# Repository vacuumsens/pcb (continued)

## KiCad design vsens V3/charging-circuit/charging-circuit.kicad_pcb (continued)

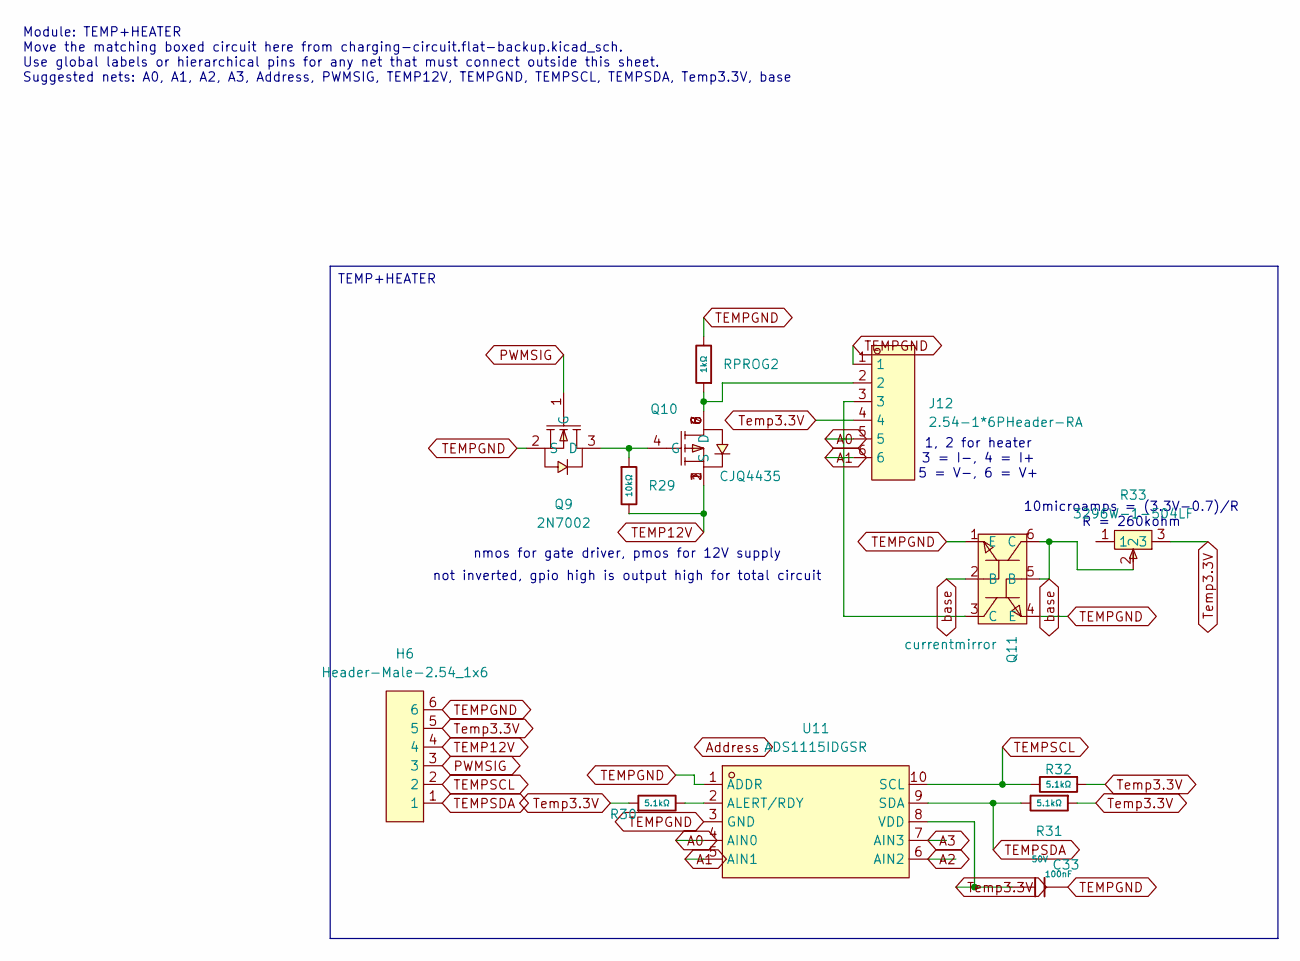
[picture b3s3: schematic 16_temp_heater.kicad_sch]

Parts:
C33: 100nF; C_0603; Voltage Rated 50V; Tolerance ±10%; Part CC0603KRX7R9BB104; LCSC C14663
H6: Header-Male-2.54_1x6; HDR-TH_6P-P2.54-V-M-1; LCSC Part C37208
J12: 2.54-1*6PHeader-RA; HDR-TH_6P-P2.54-H-M-W10.0; LCSC Part C56816
Q9: 2N7002; SOT-23-3_L2.9-W1.3-P1.90-LS2.4-BR; LCSC Part C8545
Q10: CJQ4435; SOP-8_L5.0-W4.0-P1.27-LS6.2-BL; LCSC Part C114076
Q11: currentmirror; SOT-363-6_L2.2-W1.3-P0.65-LS2.1-BL; LCSC Part C41375126
R29: 10kΩ; R_0603; Overload Voltage (Max) 75V; Tolerance ±1%; Part 0603WAF1002T5E; LCSC C25804
R30, R31, R32: 5.1kΩ; R_0603; Overload Voltage (Max) 75V; Tolerance ±1%; Part 0603WAF5101T5E; LCSC C23186
R33: 3296W-1-504LF; RES-ADJ-TH_3296W; LCSC Part C83694
RPROG2: 1kΩ; R_0603; Overload Voltage (Max) 75V; Tolerance ±1%; Part 0603WAF1001T5E; LCSC C21190
U11: ADS1115IDGSR; MSOP-10_L3.0-W3.0-P0.50-LS5.0-BL; LCSC Part C37593

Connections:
A0: J12.5, U11.4 (AIN0)
A1: J12.6, U11.5 (AIN1)
A2: U11.6 (AIN2)
A3: U11.7 (AIN3)
unnamed: J12.2, Q10.5 (D), Q10.6 (D), Q10.7 (D), Q10.8 (D), RPROG2.1
unnamed: J12.3, Q11.3 (C)
unnamed: Q9.3 (D), Q10.4 (G), R29.1
unnamed: R30.2, U11.2 (ALERT/RDY)
PWMSIG: H6.3, Q9.1 (G)
TEMP12V: H6.4, Q10.1 (S), Q10.2 (S), Q10.3 (S), R29.2
TEMPGND: C33.2, H6.6, J12.1, Q9.2 (S), Q11.1 (E), Q11.4 (E), RPROG2.2, U11.1 (ADDR), U11.3 (GND)
TEMPSCL: H6.2, R32.2, U11.10 (SCL)
TEMPSDA: H6.1, R31.2, U11.9 (SDA)
Temp3.3V: C33.1, H6.5, J12.4, R30.1, R31.1, R32.1, R33.3, U11.8 (VDD)
base: Q11.2 (B), Q11.5 (B), Q11.6 (C), R33.2

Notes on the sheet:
1, 2 for heater 3 = I-, 4 = I+ 5 = V-, 6 = V+
10microamps = (3.3V-0.7)/R R = 260kohm
not inverted, gpio high is output high for total circuit
Module: TEMP+HEATER Move the matching boxed circuit here from charging-circuit.flat-backup.kicad_sch. Use global labels or hierarchical pins for any net that must connect outside this sheet. Suggested nets: A0, A1, A2, A3, Address, PWMSIG, TEMP12V, TEMPGND, TEMPSCL, TEMPSDA, Temp3.3V, base
nmos for gate driver, pmos for 12V supply
TEMP+HEATER

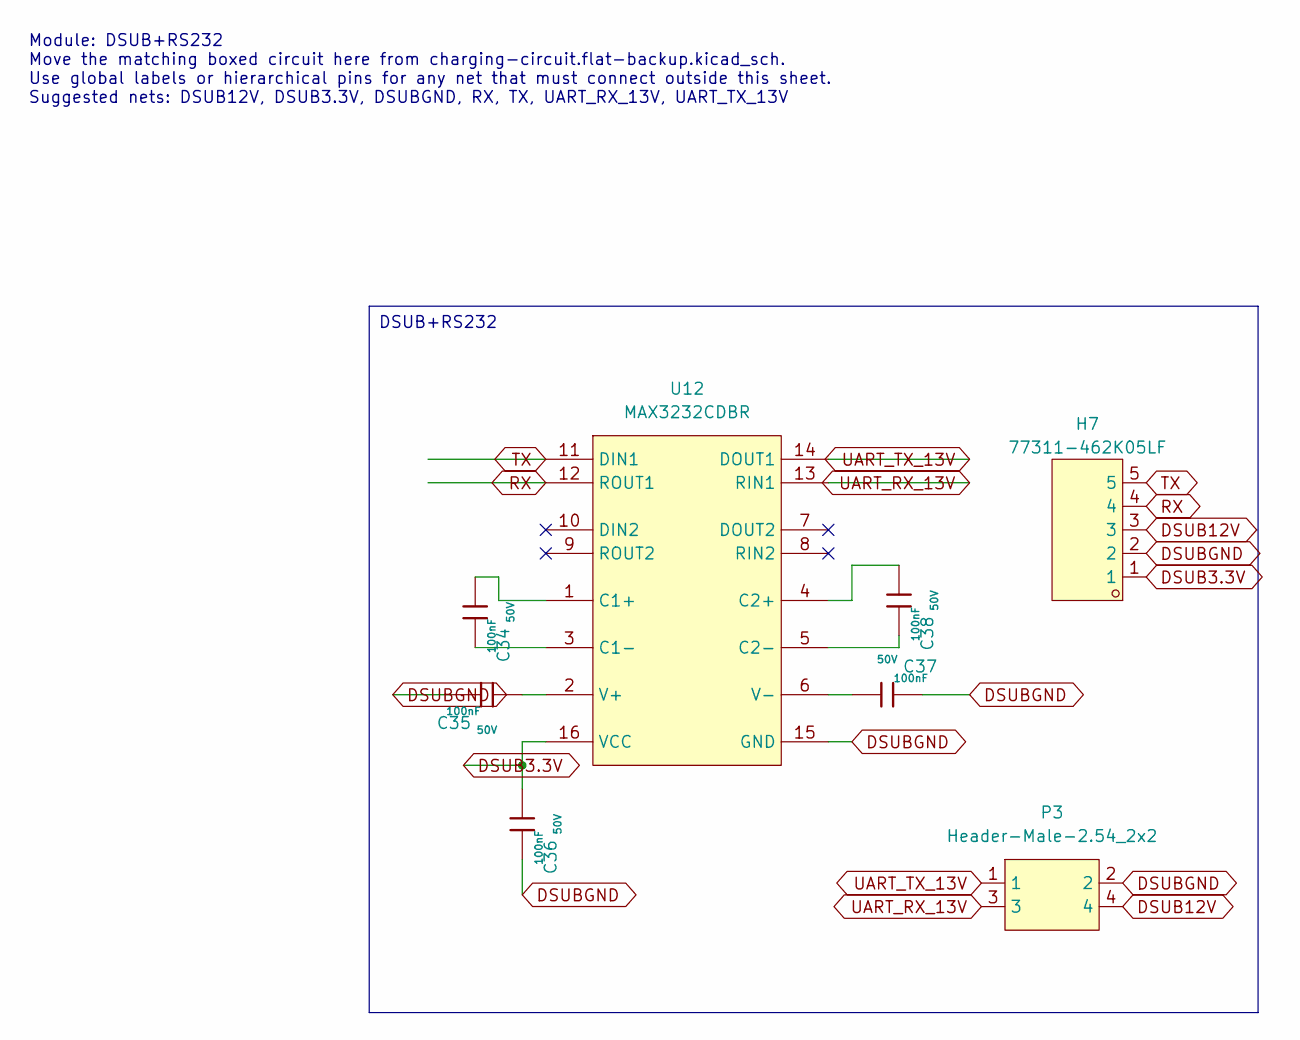
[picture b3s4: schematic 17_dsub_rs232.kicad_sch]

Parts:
C34, C35, C36, C37, C38: 100nF; C_0603; Voltage Rated 50V; Tolerance ±10%; Part CC0603KRX7R9BB104; LCSC C14663
H7: 77311-462K05LF; HDR-TH_5P-P2.54-V-M; LCSC Part C180219
P3: Header-Male-2.54_2x2; HDR-TH_4P-P2.54-V-M-R2-C2-S2.54-1; LCSC Part C66690
U12: MAX3232CDBR; SSOP-16_L6.2-W5.3-P0.65-LS7.8-BL; LCSC Part C7257

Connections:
DSUB3.3V: C36.1, H7.1, U12.16 (VCC)
DSUB12V: H7.3, P3.4
DSUBGND: C35.2, C36.2, C37.2, H7.2, P3.2, U12.15 (GND)
unnamed: C34.1, U12.1 (C1+)
unnamed: C34.2, U12.3 (C1-)
unnamed: C38.1, U12.4 (C2+)
unnamed: C38.2, U12.5 (C2-)
unnamed: C35.1, U12.2 (V+)
unnamed: C37.1, U12.6 (V-)
RX: H7.4, U12.12 (ROUT1)
TX: H7.5, U12.11 (DIN1)
UART_RX_13V: P3.3, U12.13 (RIN1)
UART_TX_13V: P3.1, U12.14 (DOUT1)

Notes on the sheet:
Module: DSUB+RS232 Move the matching boxed circuit here from charging-circuit.flat-backup.kicad_sch. Use global labels or hierarchical pins for any net that must connect outside this sheet. Suggested nets: DSUB12V, DSUB3.3V, DSUBGND, RX, TX, UART_RX_13V, UART_TX_13V
DSUB+RS232

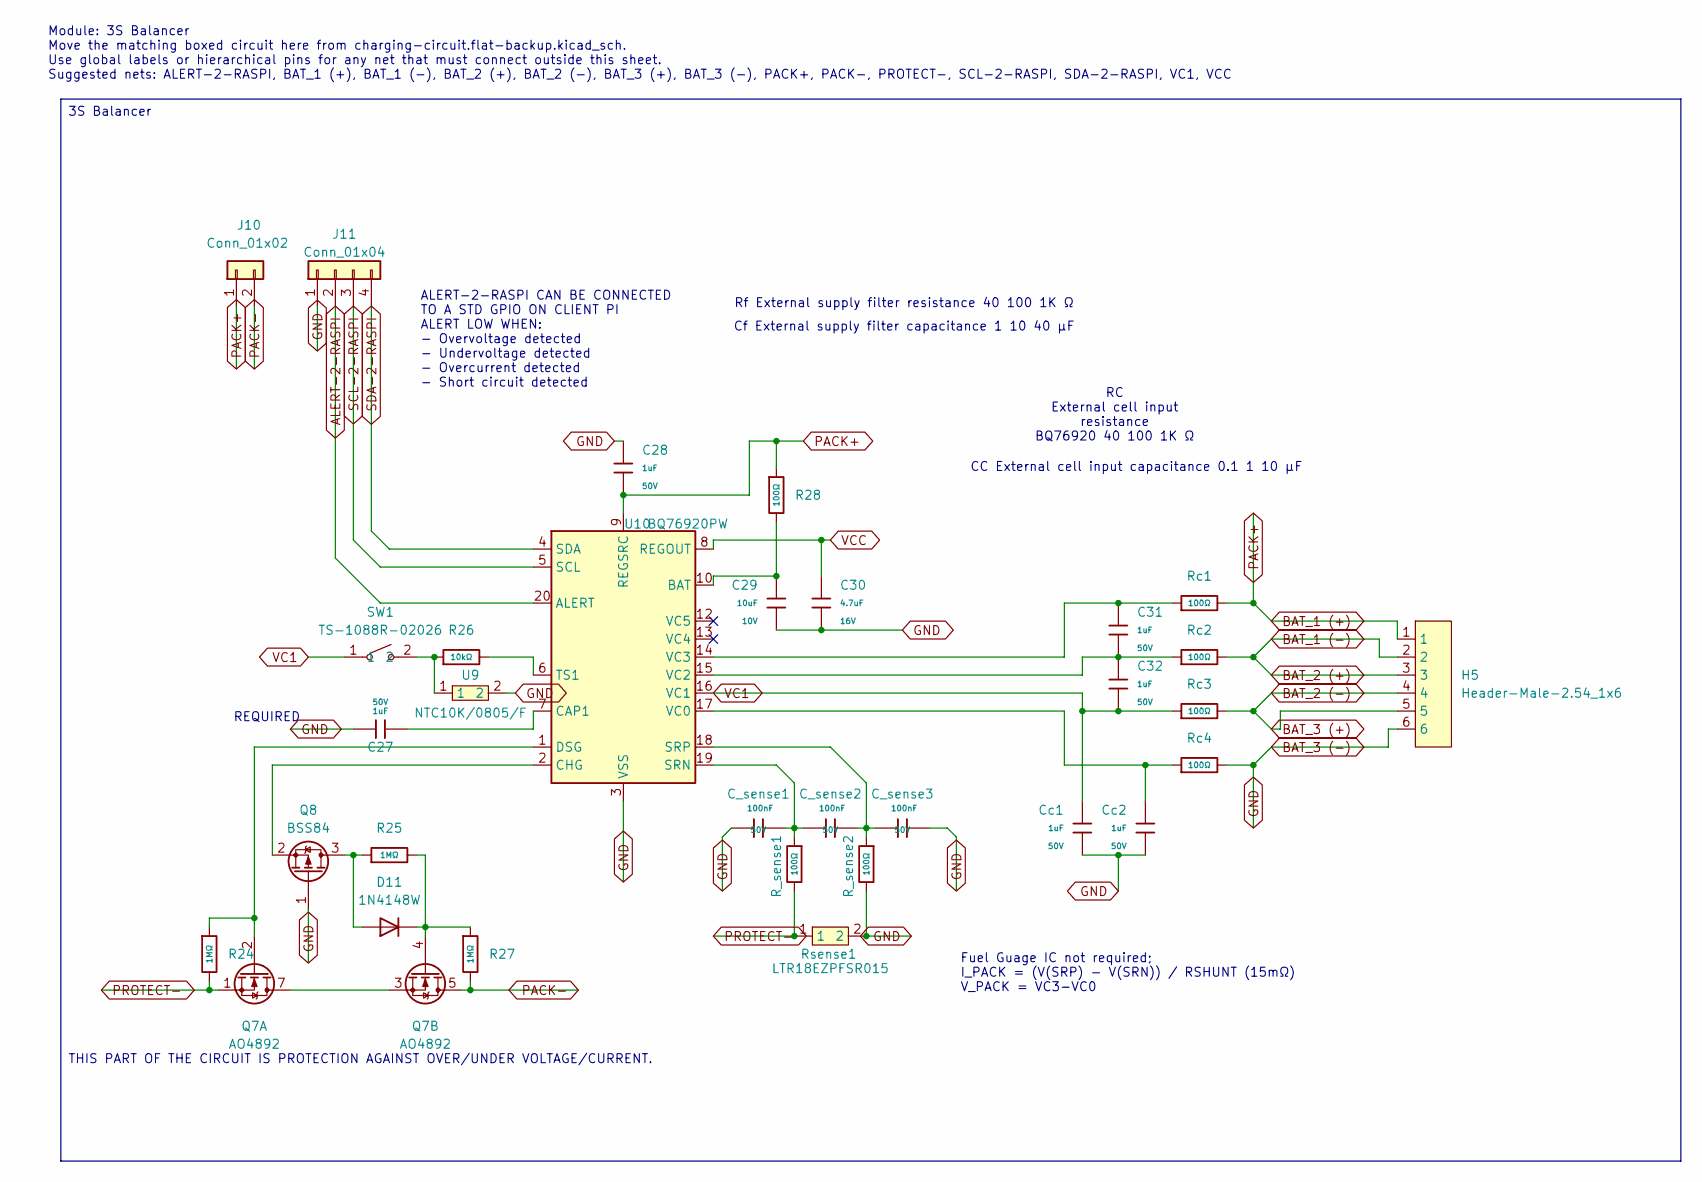
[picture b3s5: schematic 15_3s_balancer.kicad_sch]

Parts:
C27: 1uF; C_1206; Voltage Rated 50V; Tolerance ±10%; Part CL31B105KBHNNNE; LCSC C1848
C28, C31, C32: 1uF; C_0603; Voltage Rated 50V; Tolerance ±10%; Part CL10A105KB8NNNC; LCSC C15849
C29: 10uF; C_0603; Voltage Rated 10V; Tolerance ±10%; Part CL10A106KP8NNNC; LCSC C19702
C30: 4.7uF; C_0603; Voltage Rated 16V; Tolerance ±10%; Part CL10A475KO8NNNC; LCSC C19666
C_sense1, C_sense2, C_sense3: 100nF; C_0603; Voltage Rated 50V; Tolerance ±10%; Part CC0603KRX7R9BB104; LCSC C14663
Cc1, Cc2: 1uF; C_0603; Voltage Rated 50V; Tolerance ±10%; Part CL10A105KB8NNNC; LCSC C15849
D11: 1N4148W; D_SOD-123
H5: Header-Male-2.54_1x6; HDR-TH_6P-P2.54-V-M-1; LCSC Part C37208
J10: Conn_01x02; PinHeader_1x02_P2.54mm_Vertical; LCSC Part C5360898
J11: Conn_01x04; PinHeader_1x04_P2.54mm_Vertical; LCSC Part C5116483
Q7: AO4892; SOIC-8_3.9x4.9mm_P1.27mm; LCSC Part C357830
Q8: BSS84; SOT-23; LCSC Part C82079
R24, R25, R27: 1MΩ; R_0603; Overload Voltage (Max) 75V; Tolerance ±1%; Part 0603WAF1004T5E; LCSC C22935
R26: 10kΩ; R_0603; Overload Voltage (Max) 75V; Tolerance ±1%; Part 0603WAF1002T5E; LCSC C25804
R28: 100Ω; R_0603; Overload Voltage (Max) 75V; Tolerance ±1%; Part 0603WAF1000T5E; LCSC C22775
R_sense1, R_sense2: 100Ω; R_0603; Overload Voltage (Max) 75V; Tolerance ±1%; Part 0603WAF1000T5E; LCSC C22775
Rc1, Rc2, Rc3, Rc4: 100Ω; R_0603; Overload Voltage (Max) 75V; Tolerance ±1%; Part 0603WAF1000T5E; LCSC C22775
Rsense1: LTR18EZPFSR015; R0612; LCSC Part C510175
SW1: TS-1088R-02026; SW-SMD_L3.9-W3.0-P4.45; LCSC Part C455280
U9: NTC10K/0805/F; R0805; LCSC Part C9900005726
U10: BQ76920PW; TSSOP-20_4.4x6.5mm_P0.65mm

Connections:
ALERT-2-RASPI: J11.2, U10.20 (ALERT)
BAT_1 (+): C28.2, H5.1, J10.1, R28.1, Rc1.2, U10.9 (REGSRC)
BAT_1 (-): H5.2, H5.3, Rc2.2
BAT_2 (-): H5.4, H5.5, Rc3.2
BAT_3 (-): C27.1, C28.1, C29.1, C30.2, C_sense1.1, C_sense3.2, Cc1.2, Cc2.2, H5.6, J11.1, Q8.1 (G), R_sense2.2, Rc4.2, Rsense1.2, U9.2, U10.3 (VSS)
unnamed: D11.2 (A), Q8.3 (D), R25.1
unnamed: D11.1 (K), Q7.4 (G2), R25.2, R27.1
unnamed: Q7.2 (G1), R24.1, U10.1 (DSG)
unnamed: Q7.3 (S2), Q7.7 (D1), Q7.8 (D1)
unnamed: Q8.2 (S), U10.2 (CHG)
unnamed: R26.1, SW1.2, U9.1
unnamed: C29.2, R28.2, U10.10 (BAT)
unnamed: C27.2, U10.7 (CAP1)
unnamed: C_sense1.2, C_sense2.1, R_sense1.1, U10.19 (SRN)
unnamed: C_sense2.2, C_sense3.1, R_sense2.1, U10.18 (SRP)
unnamed: R26.2, U10.6 (TS1)
unnamed: Cc2.1, Rc4.1, U10.17 (VC0)
unnamed: C31.2, C32.1, Rc2.1, U10.15 (VC2)
unnamed: C31.1, Rc1.1, U10.14 (VC3)
PACK-: J10.2, Q7.5 (D2), Q7.6 (D2), R27.2
PROTECT-: Q7.1 (S1), R24.2, R_sense1.2, Rsense1.1
SCL-2-RASPI: J11.3, U10.5 (SCL)
SDA-2-RASPI: J11.4, U10.4 (SDA)
VC1: C32.2, Cc1.1, Rc3.1, SW1.1, U10.16 (VC1)
VCC: C30.1, U10.8 (REGOUT)

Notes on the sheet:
CC External cell input capacitance 0.1 1 10 µF
RC External cell input resistance BQ76920 40 100 1K Ω
REQUIRED
ALERT-2-RASPI CAN BE CONNECTED TO A STD GPIO ON CLIENT PI ALERT LOW WHEN: - Overvoltage detected - Undervoltage detected - Overcurrent detected - Short circuit detected
THIS PART OF THE CIRCUIT IS PROTECTION AGAINST OVER/UNDER VOLTAGE/CURRENT.
Rf External supply filter resistance 40 100 1K Ω
Cf External supply filter capacitance 1 10 40 µF
Module: 3S Balancer Move the matching boxed circuit here from charging-circuit.flat-backup.kicad_sch. Use global labels or hierarchical pins for any net that must connect outside this sheet. Suggested nets: ALERT-2-RASPI, BAT_1 (+), BAT_1 (-), BAT_2 (+), BAT_2 (-), BAT_3 (+), BAT_3 (-), PACK+, PACK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
Fuel Guage IC not required; I_PACK = (V(SRP) - V(SRN)) / RSHUNT (15mΩ) V_PACK = VC3-VC0
3S Balancer

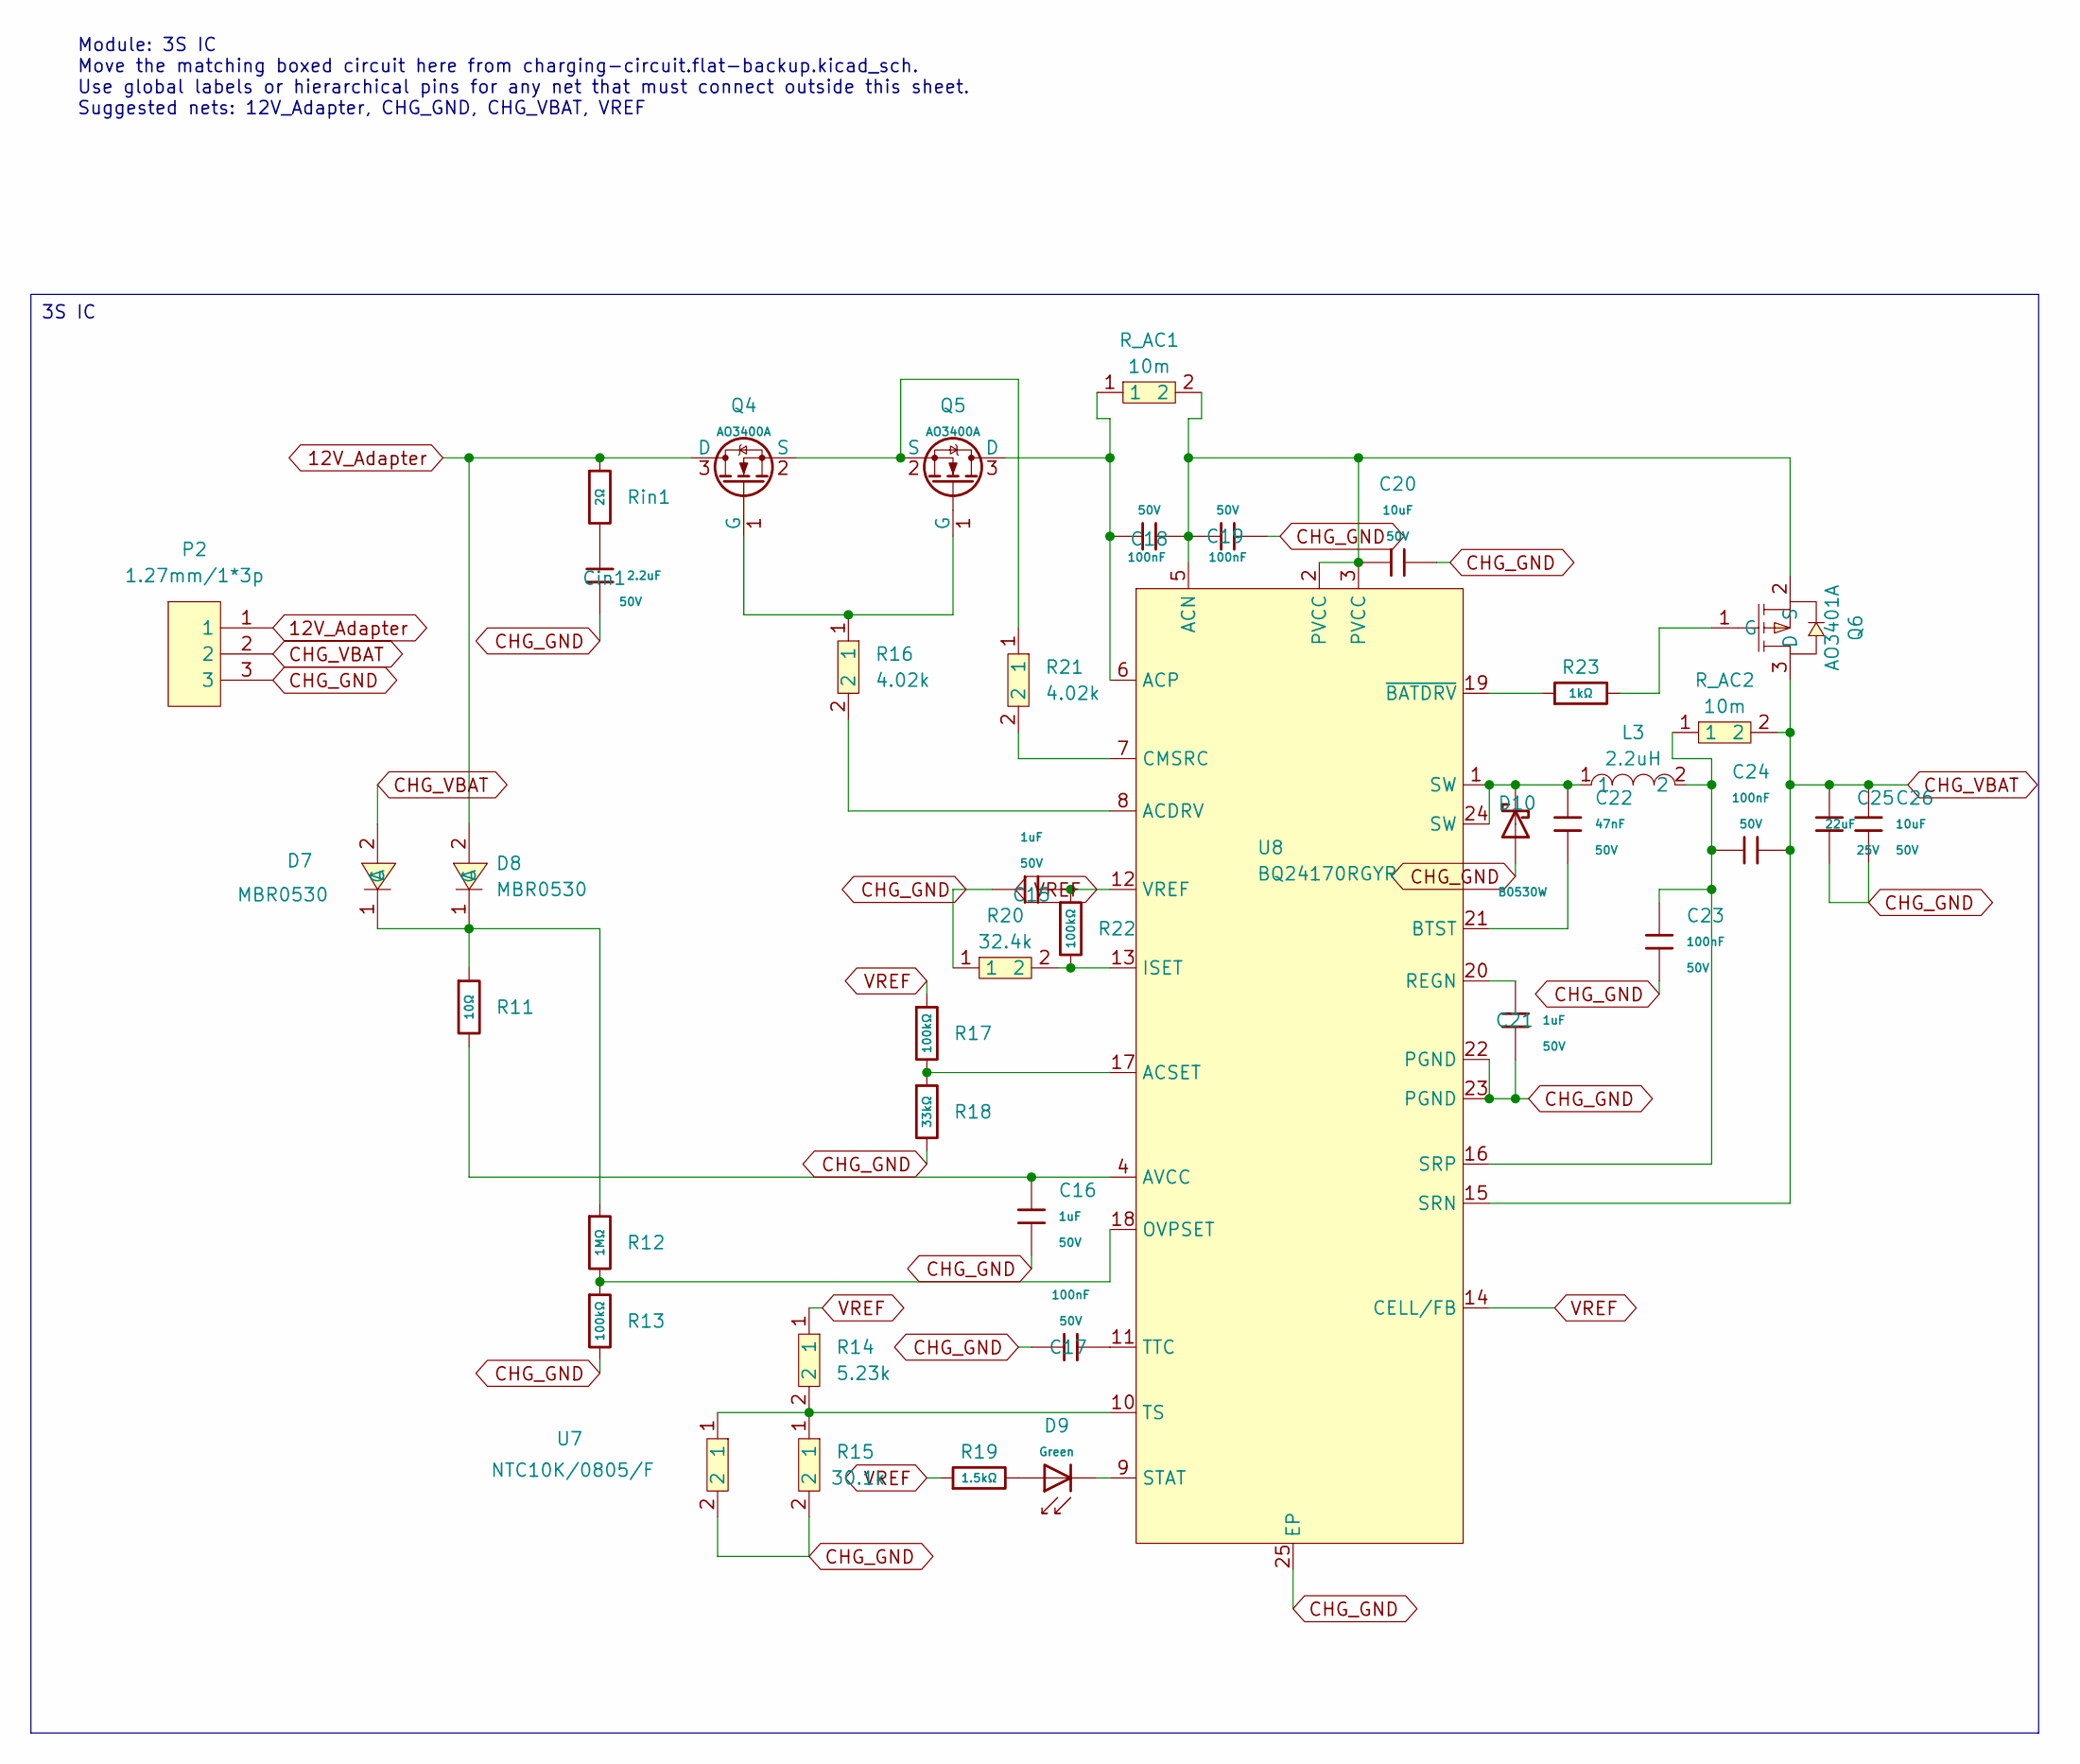
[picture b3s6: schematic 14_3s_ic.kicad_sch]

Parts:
C15, C16, C21: 1uF; C_0603; Voltage Rated 50V; Tolerance ±10%; Part CL10A105KB8NNNC; LCSC C15849
C17, C18, C19, C23, C24: 100nF; C_0603; Voltage Rated 50V; Tolerance ±10%; Part CC0603KRX7R9BB104; LCSC C14663
C20, C26: 10uF; C_1206; Voltage Rated 50V; Tolerance ±10%; Part CL31A106KBHNNNE; LCSC C13585
C22: 47nF; C_0603; Voltage Rated 50V; Tolerance ±10%; Part CL10B473KB8NNNC; LCSC C1622
C25: 22uF; C_0805; Voltage Rated 25V; Tolerance ±20%; Part CL21A226MAQNNNE; LCSC C45783
Cin1: 2.2uF; C_0805; Voltage Rated 50V; Tolerance ±10%; Part CL21A225KBQNNNE; LCSC C377773
D7, D8: MBR0530; SOD-123_L2.8-W1.8-LS3.7-RD; LCSC Part C77336
D9: Green; D_0805; Part KT-0805G; LCSC C2297
D10: B0530W; D_SOD-123; Part B0530W; LCSC C7502708
L3: 2.2uH; IND-SMD_L6.7-W6.6; LCSC Part C1329579
P2: 1.27mm/1*3p; HDR-TH_3P-P1.27-V-M-1; LCSC Part C24980
Q4, Q5: AO3400A; Q_SOT-23; Part AO3400A; LCSC C20917
Q6: AO3401A; SOT-23_L2.9-W1.3-P1.90-LS2.4-BR; LCSC Part C15127
R11: 10Ω; R_0402; Overload Voltage (Max) 50V; Tolerance ±1%; Part 0402WGF100JTCE; LCSC C25077
R12: 1MΩ; R_0603; Overload Voltage (Max) 75V; Tolerance ±1%; Part 0603WAF1004T5E; LCSC C22935
R13, R17, R22: 100kΩ; R_0603; Overload Voltage (Max) 75V; Tolerance ±1%; Part 0603WAF1003T5E; LCSC C25803
R14: 5.23k; R0805; LCSC Part C17739
R15: 30.1k; R0603; LCSC Part C23000
R16, R21: 4.02k; R0603; LCSC Part C13211
R18: 33kΩ; R_0402; Overload Voltage (Max) 50V; Tolerance ±1%; Part 0402WGF3302TCE; LCSC C25779
R19: 1.5kΩ; R_0402; Overload Voltage (Max) 50V; Tolerance ±1%; Part 0402WGF1501TCE; LCSC C25867
R20: 32.4k; R0603; LCSC Part C13187
R23: 1kΩ; R_0603; Overload Voltage (Max) 75V; Tolerance ±1%; Part 0603WAF1001T5E; LCSC C21190
R_AC1, R_AC2: 10m; R1206; LCSC Part C105362
Rin1: 2Ω; R_0603; Overload Voltage (Max) 75V; Tolerance ±1%; Part 0603WAF200KT5E; LCSC C22977
U7: NTC10K/0805/F; R0805; LCSC Part C9900005726
U8: BQ24170RGYR; VQFN-24_L5.5-W3.5-P0.50-BL-EP-2; LCSC Part C116999

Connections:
12V_Adapter: D8.2 (A), P2.1, Q4.3 (D), Rin1.1
CHG_GND: C15.2, C16.2, C17.1, C19.2, C20.2, C21.2, C23.2, C25.2, C26.2, Cin1.2, D10.2, P2.3, R13.2, R15.2, R18.2, R20.1, U7.2, U8.22 (PGND), U8.23 (PGND), U8.25 (EP)
CHG_VBAT: C24.1, C25.1, C26.1, D7.2 (A), P2.2, Q6.3 (D), R_AC2.2, U8.15 (SRN)
unnamed: C22.1, D10.1, L3.1, U8.1 (SW), U8.24 (SW)
unnamed: Cin1.1, Rin1.2
unnamed: D7.1 (C), D8.1 (C), R11.1, R12.1
unnamed: D9.2, R19.2
unnamed: Q4.1 (G), Q5.1 (G), R16.1
unnamed: Q4.2 (S), Q5.2 (S), R21.1
unnamed: C18.1, Q5.3 (D), R_AC1.1, U8.6 (ACP)
unnamed: Q6.1 (G), R23.2
unnamed: C18.2, C19.1, C20.1, Q6.2 (S), R_AC1.2, U8.2 (PVCC), U8.3 (PVCC), U8.5 (ACN)
unnamed: R16.2, U8.8 (ACDRV)
unnamed: R17.2, R18.1, U8.17 (ACSET)
unnamed: C16.1, R11.2, U8.4 (AVCC)
unnamed: C22.2, U8.21 (BTST)
unnamed: R21.2, U8.7 (CMSRC)
unnamed: R20.2, R22.2, U8.13 (ISET)
unnamed: R12.2, R13.1, U8.18 (OVPSET)
unnamed: C21.1, U8.20 (REGN)
unnamed: C23.1, C24.2, L3.2, R_AC2.1, U8.16 (SRP)
unnamed: D9.1, U8.9 (STAT)
unnamed: R14.2, R15.1, U7.1, U8.10 (TS)
unnamed: C17.2, U8.11 (TTC)
unnamed: R23.1, U8.19 (~BATDRV)
VREF: C15.1, R14.1, R17.1, R19.1, R22.1, U8.12 (VREF), U8.14 (CELL/FB)

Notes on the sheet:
Module: 3S IC Move the matching boxed circuit here from charging-circuit.flat-backup.kicad_sch. Use global labels or hierarchical pins for any net that must connect outside this sheet. Suggested nets: 12V_Adapter, CHG_GND, CHG_VBAT, VREF
3S IC

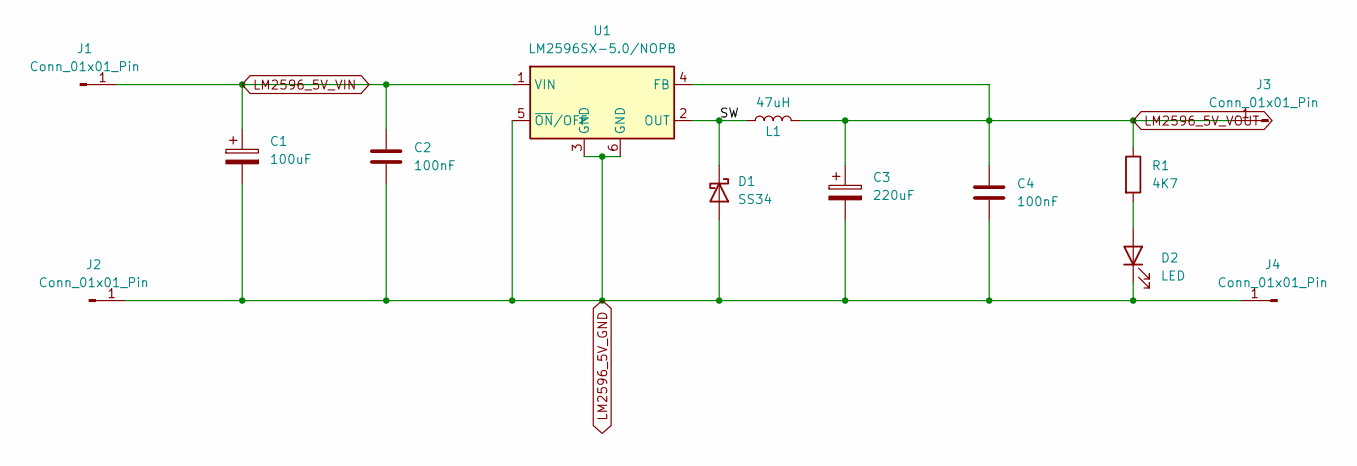
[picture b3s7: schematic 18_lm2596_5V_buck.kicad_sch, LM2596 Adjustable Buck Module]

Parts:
C1: 100uF; CP_Elec_8x10
C2, C4: 100nF; C_0603_1608Metric
C3: 220uF; CP_Elec_8x10
D1: SS34; D_SMA
D2: LED; LED_0603_1608Metric
J1, J2, J3, J4: Conn_01x01_Pin; PinHeader_1x01_P2.54mm_Vertical
L1: 47uH; L_Bourns_SRR1208_12.7x12.7mm
R1: 4K7; R_0603_1608Metric
U1: LM2596SX-5.0/NOPB; TO-263-5_L10.2-W8.9-P1.70-TL; MPN LM2596SX-5.0/NOPB; LCSC Part C10002

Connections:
/LM2596 5V Buck/SW: D1.1 (K), L1.1, U1.2 (OUT); also elsewhere on the board
unnamed: D2.2 (A), R1.2

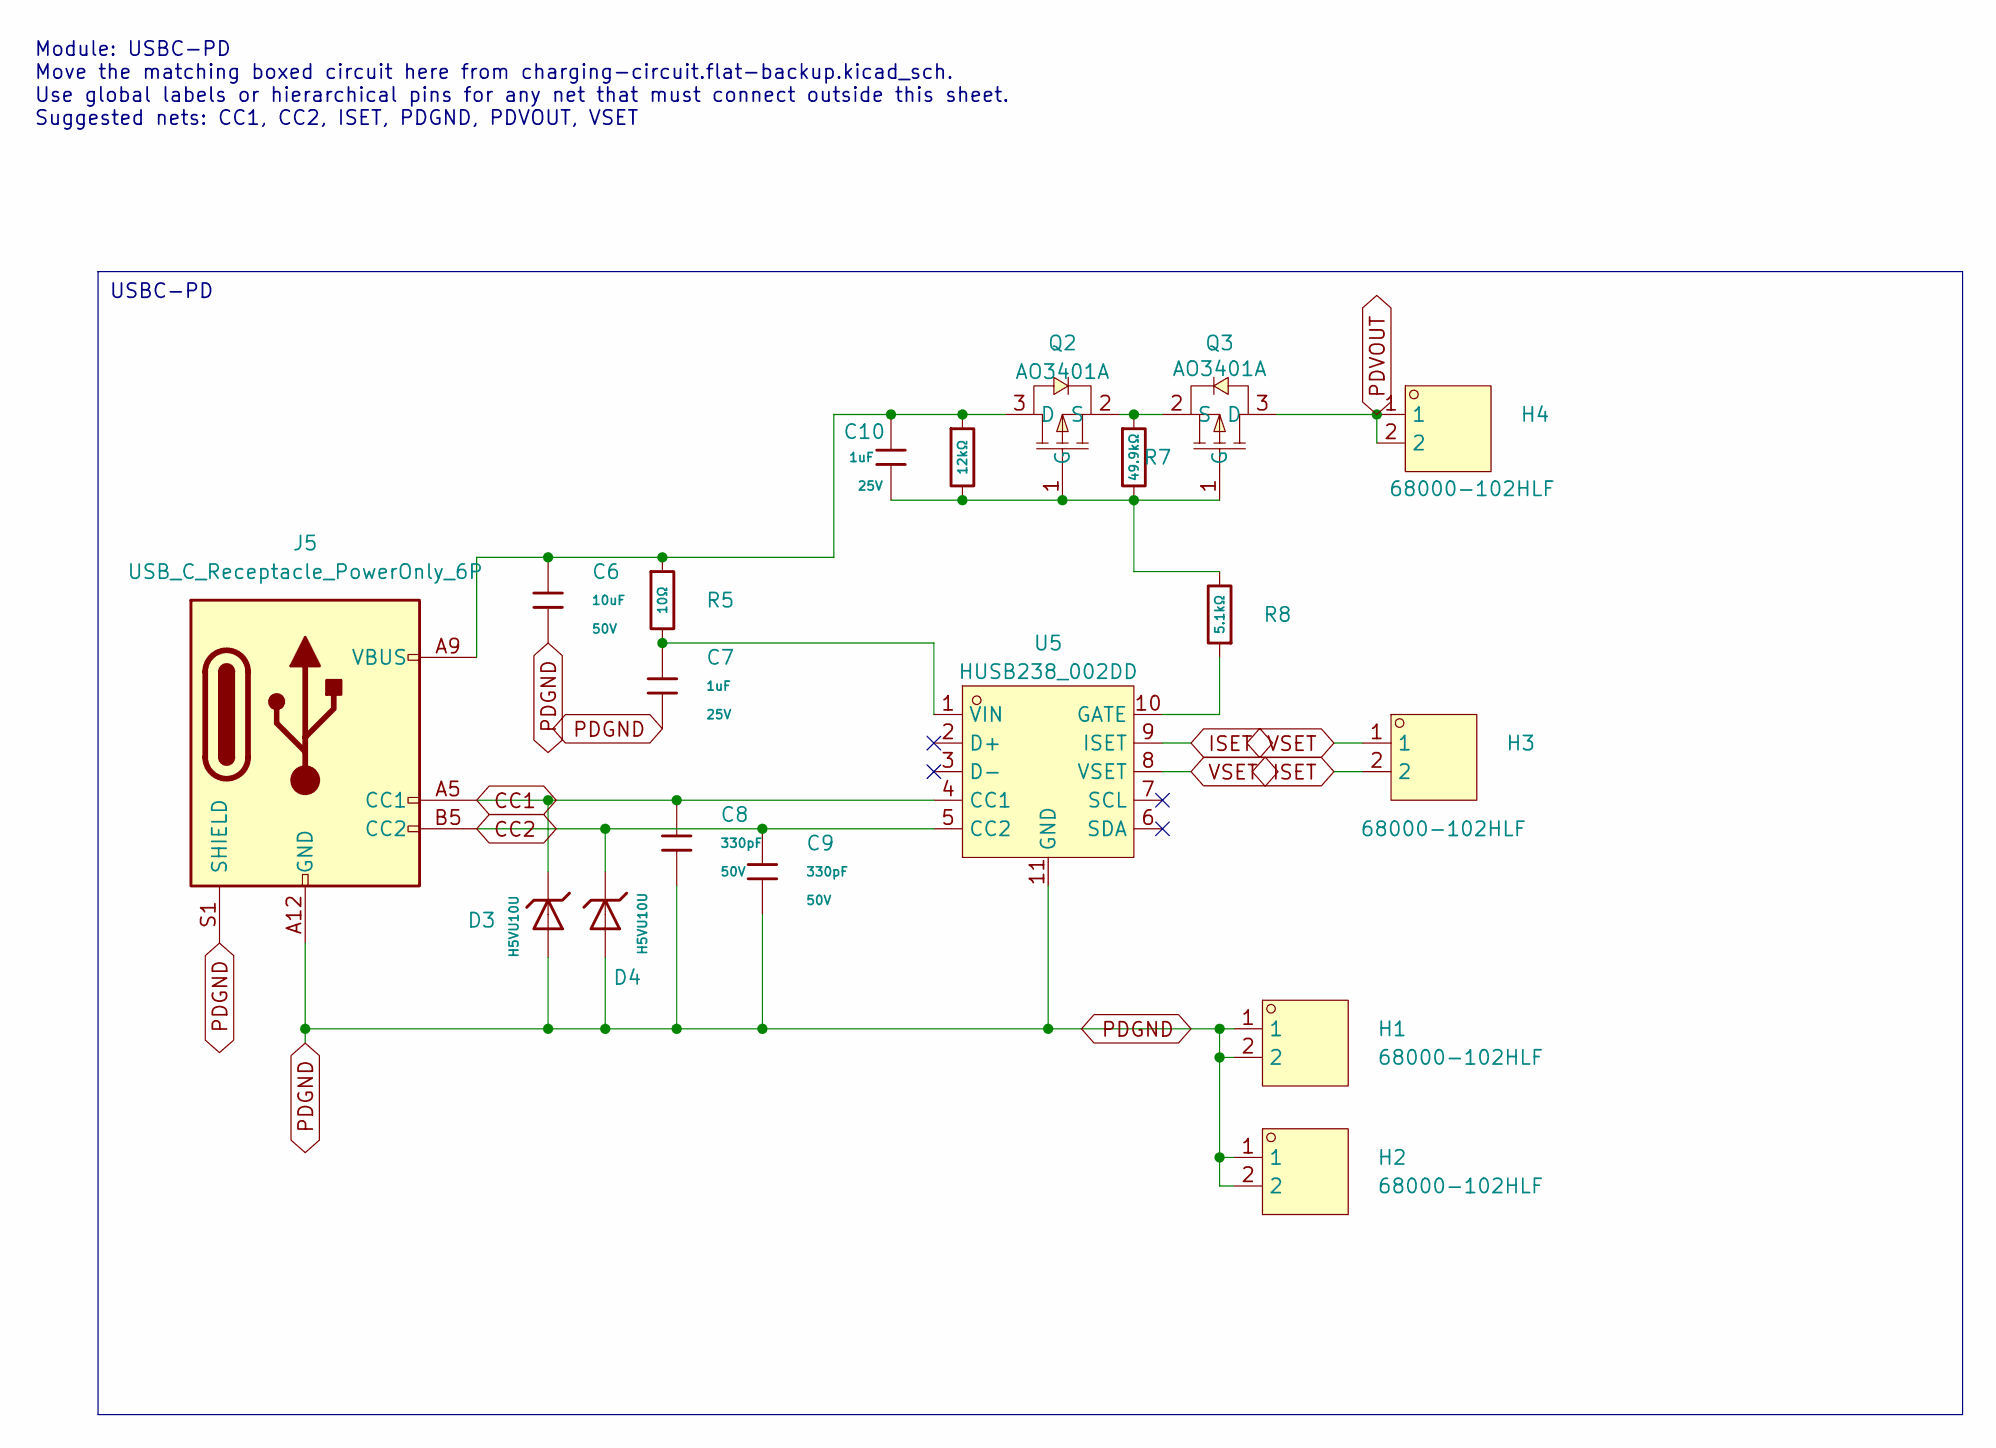
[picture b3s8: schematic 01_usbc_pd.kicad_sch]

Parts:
C6: 10uF; C_1206; Voltage Rated 50V; Tolerance ±10%; Part CL31A106KBHNNNE; LCSC C13585
C7, C10: 1uF; C_0402; Voltage Rated 25V; Tolerance ±10%; Part CL05A105KA5NQNC; LCSC C52923
C8, C9: 330pF; C_0603; Voltage Rated 50V; Tolerance ±5%; Part CL10C331JB8NNNC; LCSC C1664
D3, D4: H5VU10U; D_DFN1006-2L; Breakdown Voltage 9V; Part H5VU10U; LCSC C22395519
H1, H2, H3, H4: 68000-102HLF; HDR-TH_2P-P2.54-V-M-1; LCSC Part C168673
J5: USB_C_Receptacle_PowerOnly_6P; TYPE-C-SMD_TYPE-C-6P; LCSC Part C283540
Q2, Q3: AO3401A; SOT-23_L2.9-W1.3-P1.90-LS2.4-BR; LCSC Part C15127
R5: 10Ω; R_0603; Overload Voltage (Max) 75V; Tolerance ±1%; Part 0603WAF100JT5E; LCSC C22859
R6: 12kΩ; R_0603; Overload Voltage (Max) 75V; Tolerance ±1%; Part 0603WAF1202T5E; LCSC C22790
R7: 49.9kΩ; R_0603; Overload Voltage (Max) 75V; Tolerance ±1%; Part 0603WAF4992T5E; LCSC C23184
R8: 5.1kΩ; R_0603; Overload Voltage (Max) 75V; Tolerance ±1%; Part 0603WAF5101T5E; LCSC C23186
U5: HUSB238_002DD; DFN-10_L3.0-W3.0-P0.50-BL-EP2.5; LCSC Part C7471904

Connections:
CC1: C8.1, D3.1, J5.A5 (CC1), U5.4 (CC1)
CC2: C9.1, D4.1, J5.B5 (CC2), U5.5 (CC2)
ISET: H3.2, U5.9 (ISET)
unnamed: C6.1, C10.2, J5.A9 (VBUS), J5.B9 (VBUS), Q2.3 (D), R5.1, R6.1
unnamed: C10.1, Q2.1 (G), Q3.1 (G), R6.2, R7.2, R8.2
unnamed: Q2.2 (S), Q3.2 (S), R7.1
unnamed: R8.1, U5.10 (GATE)
unnamed: C7.1, R5.2, U5.1 (VIN)
PDGND: C6.2, C7.2, C8.2, C9.2, D3.2, D4.2, H1.1, H1.2, H2.1, H2.2, J5.A12 (GND), J5.B12 (GND), J5.S1 (SHIELD), U5.11 (GND)
PDVOUT: H4.1, H4.2, Q3.3 (D)
VSET: H3.1, U5.8 (VSET)

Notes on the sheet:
Module: USBC-PD Move the matching boxed circuit here from charging-circuit.flat-backup.kicad_sch. Use global labels or hierarchical pins for any net that must connect outside this sheet. Suggested nets: CC1, CC2, ISET, PDGND, PDVOUT, VSET
USBC-PD

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
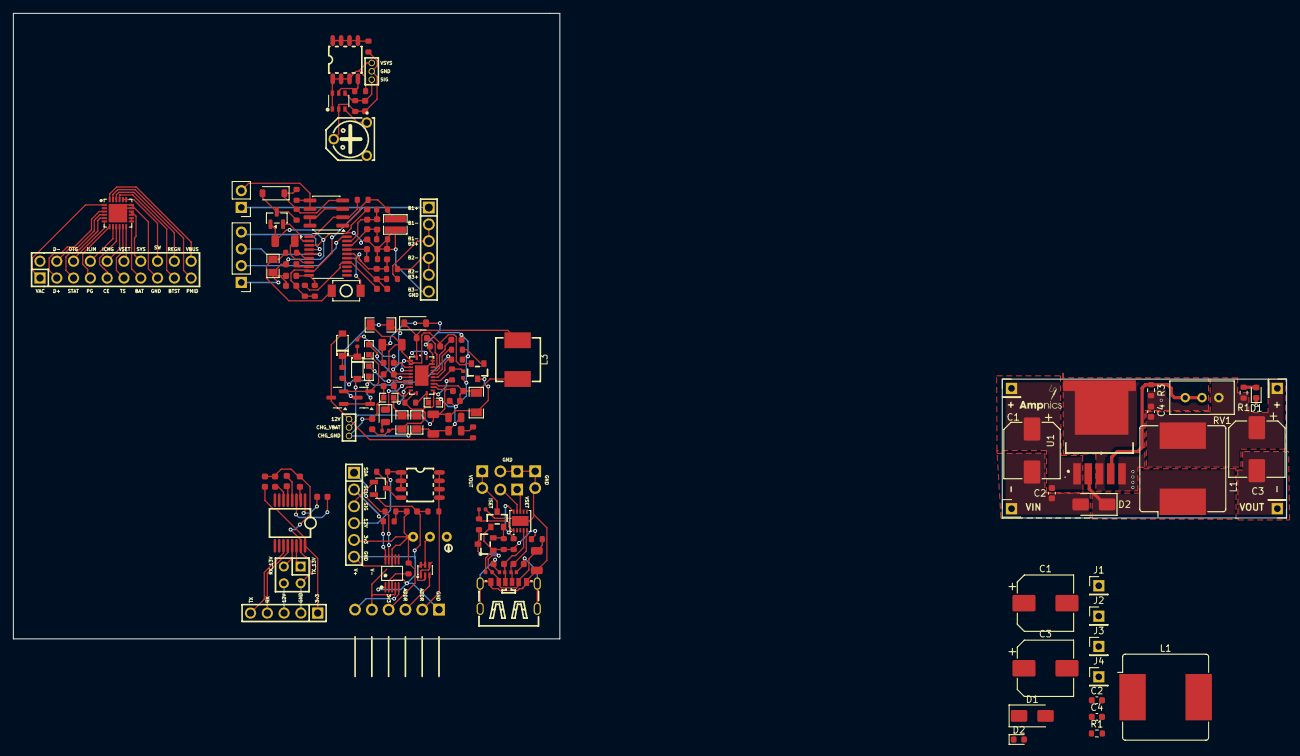
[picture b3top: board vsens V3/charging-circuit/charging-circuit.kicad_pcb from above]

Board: 2 copper layers, 82.6 x 94.6 mm, 149 parts (0 on the bottom side), 123 nets.

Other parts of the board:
C1#2: 100uF; CP_Elec_8x10
C2#2, C4#2: 100nF; C_0603_1608Metric
C3#2: 220uF; CP_Elec_8x10
D1#2: LED; LED_0603_1608Metric
D2#2: SS34; D_SMA
J1#2, J2#2, J3#2, J4#2: Conn_01x01_Pin; PinHeader_1x01_P2.54mm_Vertical
L1#2: 47uH; L_Bourns_SRR1208_12.7x12.7mm
R1#2: 4K7; R_0603_1608Metric
R3#2: 1K; R_0603_1608Metric
RV1: 10K; Potentiometer_Bourns_3296W_Vertical

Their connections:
/LM2596 5V Buck/SW: D2#2.1 (K), L1#2.1; also elsewhere on the board
unnamed: D1#2.2 (A), R1#2.2
unnamed: R3#2.1, RV1.2, RV1.3
